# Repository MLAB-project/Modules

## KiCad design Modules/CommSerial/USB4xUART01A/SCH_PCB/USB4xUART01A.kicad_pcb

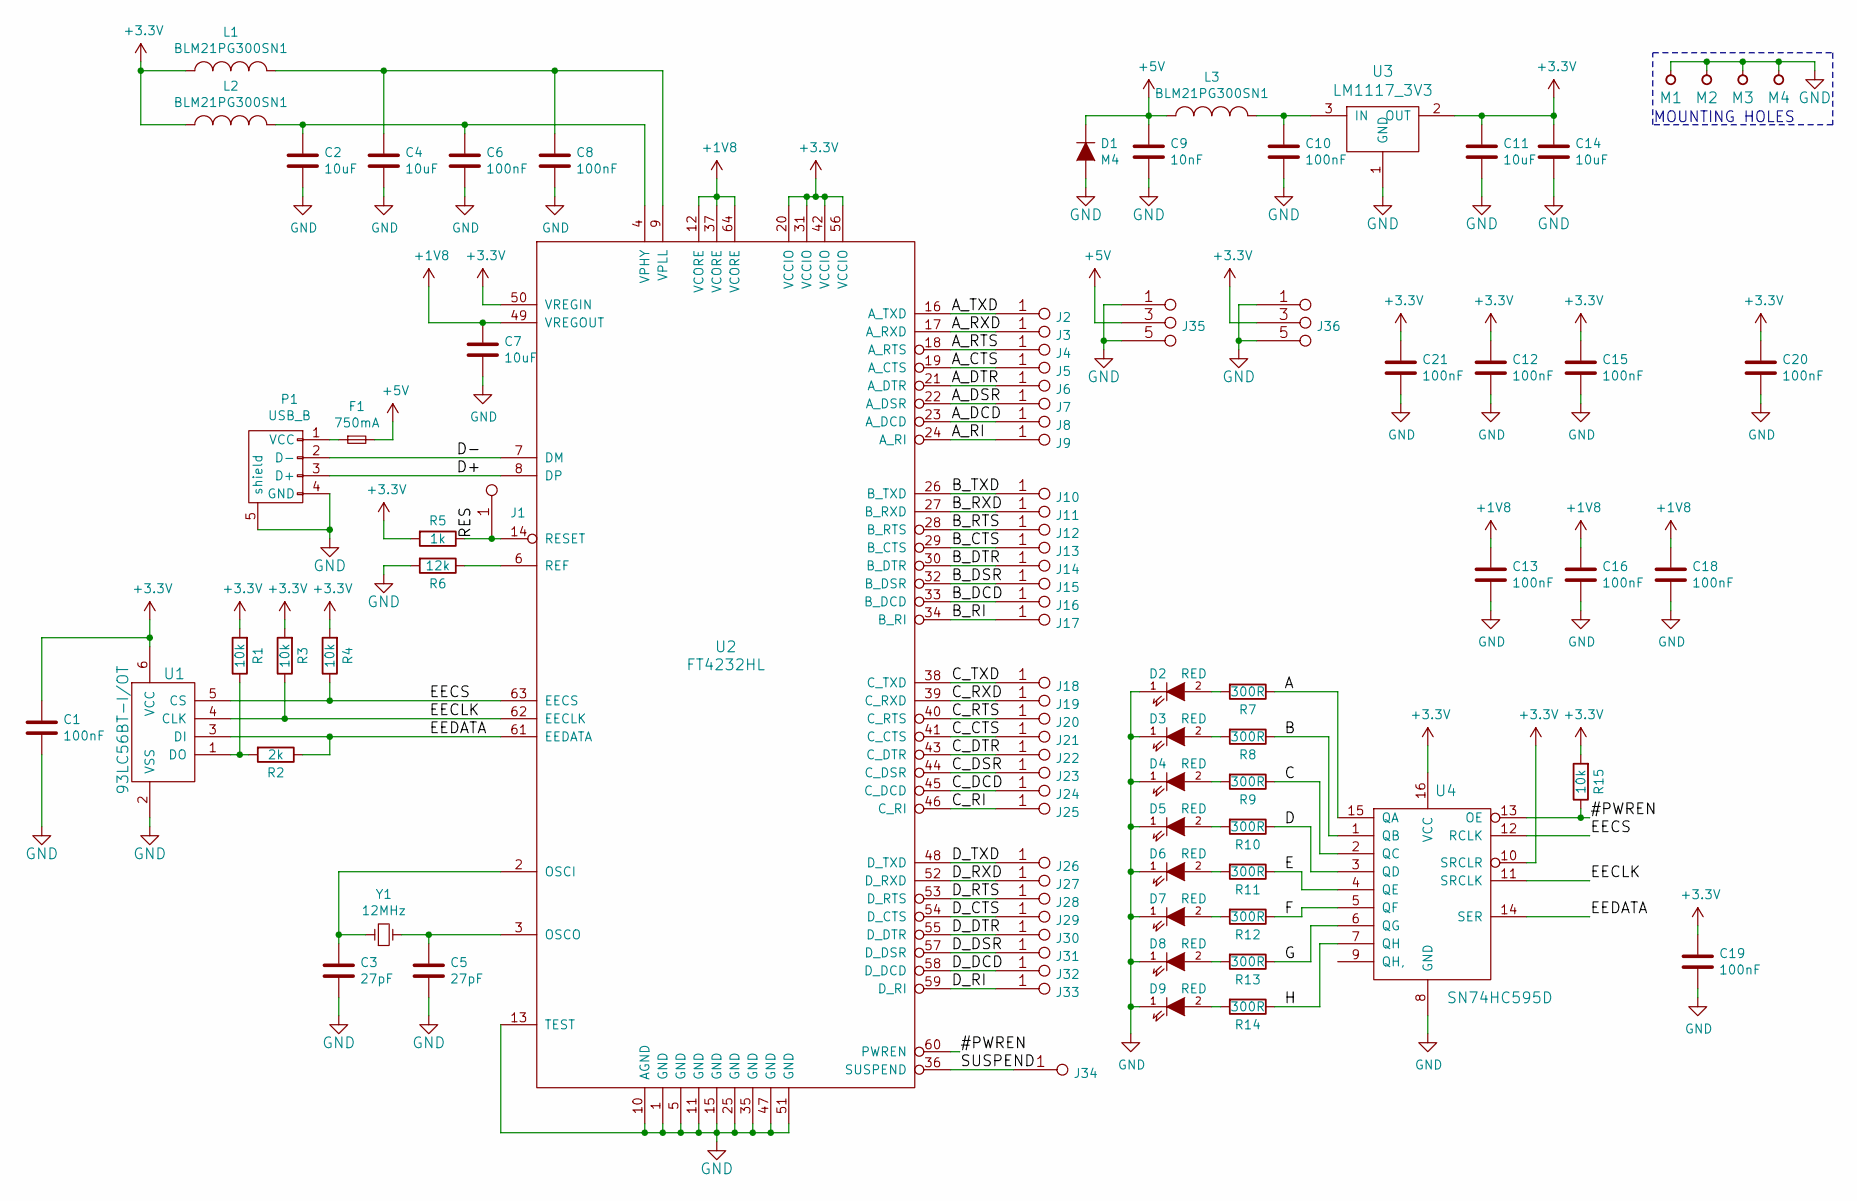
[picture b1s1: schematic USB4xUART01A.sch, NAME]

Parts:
C1, C6, C8, C10, C12, C13, C15, C16, C18, C19, C20, C21: 100nF; SMD-0805
C2, C4, C7, C11, C14: 10uF; SMD-0805
C3, C5: 27pF; SMD-0805
C9: 10nF; SMD-0805
D1: M4; Diode-SMA_Standard
D2, D3, D4, D5, D6, D7, D8, D9: RED; LED_1206
F1: 750mA; 1812
J1, J2, J3, J4, J5, J6, J7, J8, J9, J10, J11, J12, J13, J14, J15, J16, J17, J18, J19, J20, J21, J22, J23, J24, J25, J26, J27, J28, J29, J30, J31, J32, J33, J34: JUMP_2x1; Straight_1x02
J35, J36: JUMP_3X2; Straight_2x03
L1, L2, L3: BLM21PG300SN1; SMD-0805
M1, M2, M3, M4: HOLE; MountingHole_3mm
P1: USB_B
R1, R3, R4, R15: 10k; SMD-0805
R2: 2k; SMD-0805
R5: 1k; SMD-0805
R6: 12k; SMD-0805
R7, R8, R9, R10, R11, R12, R13, R14: 300R; SMD-0805
U1: 93LC56BT-I/OT; SOT-23-6
U2: FT4232HL; LQFP-64_10x10mm_Pitch0.5mm
U3: LM1117_3V3; SOT-223
U4: SN74HC595D; SO-16-N
Y1: 12MHz; Crystal_HC49-U_Vertical

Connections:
+1V8: C7.1, C13.1, C16.1, C18.1, U2.12 (VCORE), U2.37 (VCORE), U2.49 (VREGOUT), U2.64 (VCORE)
+3V3: C1.1, C11.1, C12.1, C14.1, C15.1, C19.1, C20.1, C21.1, J36.3 (4), J36.4, L1.1, L2.1, R1.2, R3.2, R4.2, R5.2, R15.2, U1.6 (VCC), U2.20 (VCCIO), U2.31 (VCCIO), U2.42 (VCCIO), U2.50 (VREGIN), U2.56 (VCCIO), U3.2 (OUT), U3.4 (OUT), U4.10 (SRCLR), U4.16 (VCC)
+5V: C9.1, D1.1 (K), F1.2, J35.3 (4), J35.4, L3.1
/#PWREN: R15.1, U2.60 (PWREN), U4.13 (OE)
/A: R7.1, U4.15 (QA)
/A_CTS: J5.1, J5.2, U2.19 (A_CTS)
/A_DCD: J8.1, J8.2, U2.23 (A_DCD)
/A_DSR: J7.1, J7.2, U2.22 (A_DSR)
/A_DTR: J6.1, J6.2, U2.21 (A_DTR)
/A_RI: J9.1, J9.2, U2.24 (A_RI)
/A_RTS: J4.1, J4.2, U2.18 (A_RTS)
/A_RXD: J3.1, J3.2, U2.17 (A_RXD)
/A_TXD: J2.1, J2.2, U2.16 (A_TXD)
/B: R8.1, U4.1 (QB)
/B_CTS: J13.1, J13.2, U2.29 (B_CTS)
/B_DCD: J16.1, J16.2, U2.33 (B_DCD)
/B_DSR: J15.1, J15.2, U2.32 (B_DSR)
/B_DTR: J14.1, J14.2, U2.30 (B_DTR)
/B_RI: J17.1, J17.2, U2.34 (B_RI)
/B_RTS: J12.1, J12.2, U2.28 (B_RTS)
/B_RXD: J11.1, J11.2, U2.27 (B_RXD)
/B_TXD: J10.1, J10.2, U2.26 (B_TXD)
/C: R9.1, U4.2 (QC)
/C_CTS: J21.1, J21.2, U2.41 (C_CTS)
/C_DCD: J24.1, J24.2, U2.45 (C_DCD)
/C_DSR: J23.1, J23.2, U2.44 (C_DSR)
/C_DTR: J22.1, J22.2, U2.43 (C_DTR)
/C_RI: J25.1, J25.2, U2.46 (C_RI)
/C_RTS: J20.1, J20.2, U2.40 (C_RTS)
/C_RXD: J19.1, J19.2, U2.39 (C_RXD)
/C_TXD: J18.1, J18.2, U2.38 (C_TXD)
/D: R10.1, U4.3 (QD)
/D+: P1.3 (D+), U2.8 (DP)
/D-: P1.2 (D-), U2.7 (DM)
/D_CTS: J29.1, J29.2, U2.54 (D_CTS)
/D_DCD: J32.1, J32.2, U2.58 (D_DCD)
/D_DSR: J31.1, J31.2, U2.57 (D_DSR)
/D_DTR: J30.1, J30.2, U2.55 (D_DTR)
/D_RI: J33.1, J33.2, U2.59 (D_RI)
/D_RTS: J28.1, J28.2, U2.53 (D_RTS)
/D_RXD: J27.1, J27.2, U2.52 (D_RXD)
/D_TXD: J26.1, J26.2, U2.48 (D_TXD)
/E: R11.1, U4.4 (QE)
/EECLK: R3.1, U1.4 (CLK), U2.62 (EECLK), U4.11 (SRCLK)
/EECS: R4.1, U1.5 (CS), U2.63 (EECS), U4.12 (RCLK)
/EEDATA: R2.1, U1.3 (DI), U2.61 (EEDATA), U4.14 (SER)
/F: R12.1, U4.5 (QF)
/G: R13.1, U4.6 (QG)
/H: R14.1, U4.7 (QH)
/RES: J1.1, J1.2, R5.1, U2.14 (RESET)
/SUSPEND: J34.1, J34.2, U2.36 (SUSPEND)
GND: C1.2, C2.2, C3.2, C4.2, C5.2, C6.2, C7.2, C8.2, C9.2, C10.2, C11.2, C12.2, C13.2, C14.2, C15.2, C16.2, C18.2, C19.2, C20.2, C21.2, D1.2 (A), D2.1 (K), D3.1 (K), D4.1 (K), D5.1 (K), D6.1 (K), D7.1 (K), D8.1 (K), D9.1 (K), J35.1 (2), J35.2, J35.5 (6), J35.6, J36.1 (2), J36.2, J36.5 (6), J36.6, M1.1, M2.1, M3.1, M4.1, P1.4 (GND), P1.5 (shield), R6.2, U1.2 (VSS), U2.1 (GND), U2.5 (GND), U2.10 (AGND), U2.11 (GND), U2.13 (TEST), U2.15 (GND), U2.25 (GND), U2.35 (GND), U2.47 (GND), U2.51 (GND), U3.1 (GND), U4.8 (GND)
unnamed: C2.1, C6.1, L2.2, U2.4 (VPHY)
unnamed: C3.1, U2.2 (OSCI), Y1.1
unnamed: C4.1, C8.1, L1.2, U2.9 (VPLL)
unnamed: C5.1, U2.3 (OSCO), Y1.2
unnamed: C10.1, L3.2, U3.3 (IN)
unnamed: D2.2 (A), R7.2
unnamed: D3.2 (A), R8.2
unnamed: D4.2 (A), R9.2
unnamed: D5.2 (A), R10.2
unnamed: D6.2 (A), R11.2
unnamed: D7.2 (A), R12.2
unnamed: D8.2 (A), R13.2
unnamed: D9.2 (A), R14.2
unnamed: F1.1, P1.1 (VCC)
unnamed: R1.1, R2.2, U1.1 (DO)
unnamed: R6.1, U2.6 (REF)

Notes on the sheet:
MOUNTING HOLES

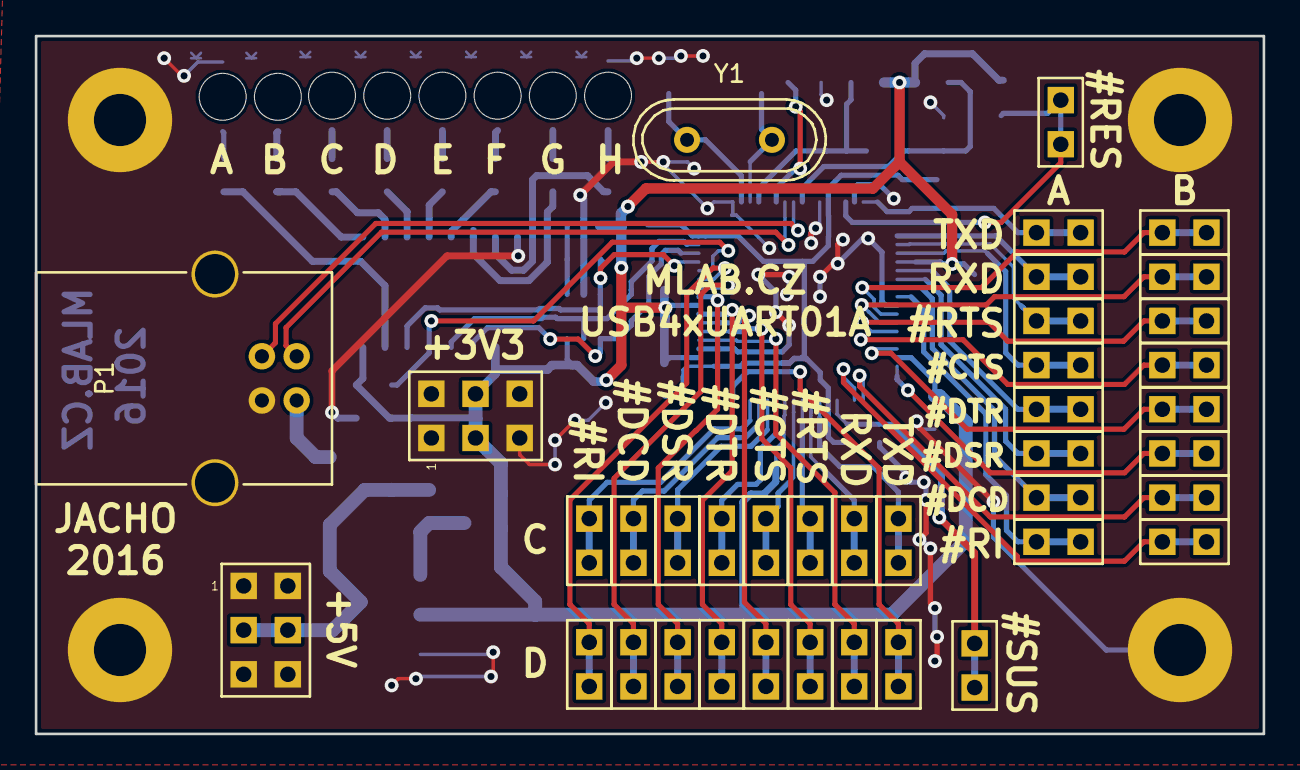
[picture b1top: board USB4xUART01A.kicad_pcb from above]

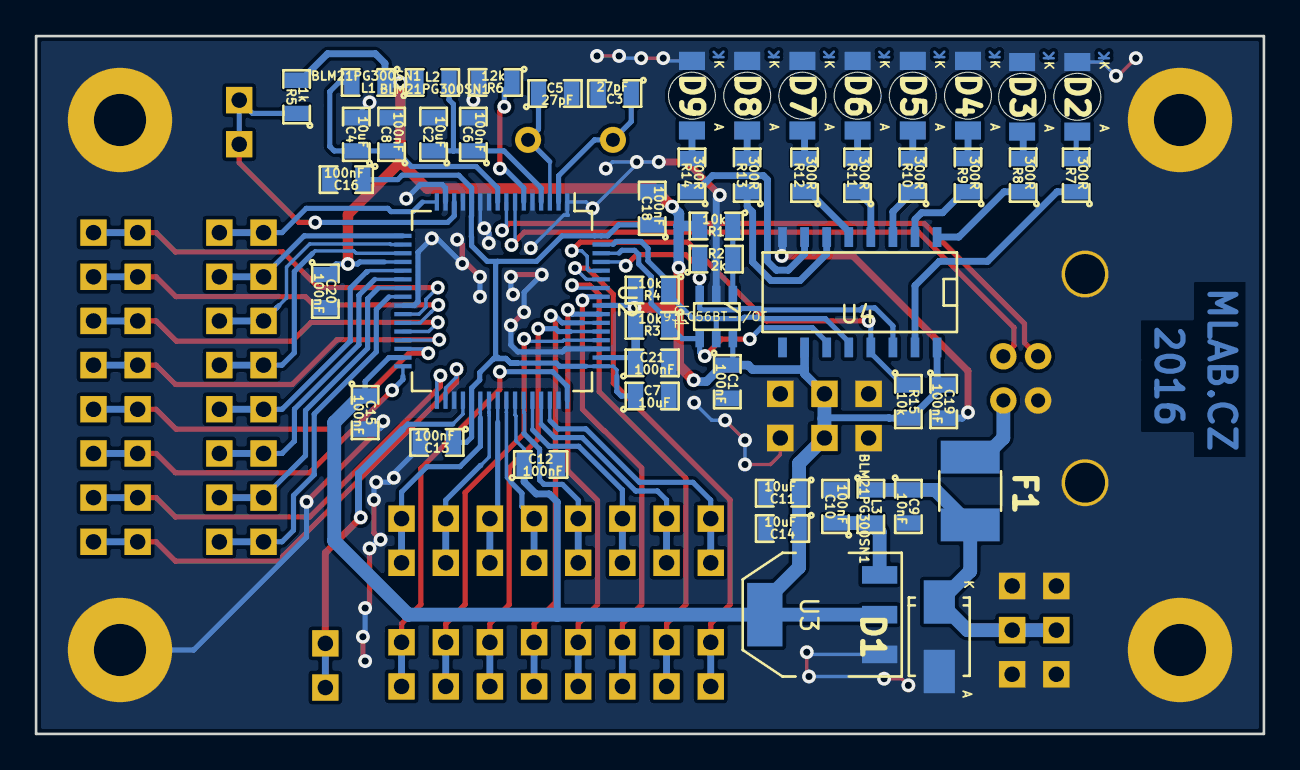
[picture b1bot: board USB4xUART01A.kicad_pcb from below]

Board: 2 copper layers, 70.6 x 40.1 mm, 94 parts (52 on the bottom side), 68 nets.

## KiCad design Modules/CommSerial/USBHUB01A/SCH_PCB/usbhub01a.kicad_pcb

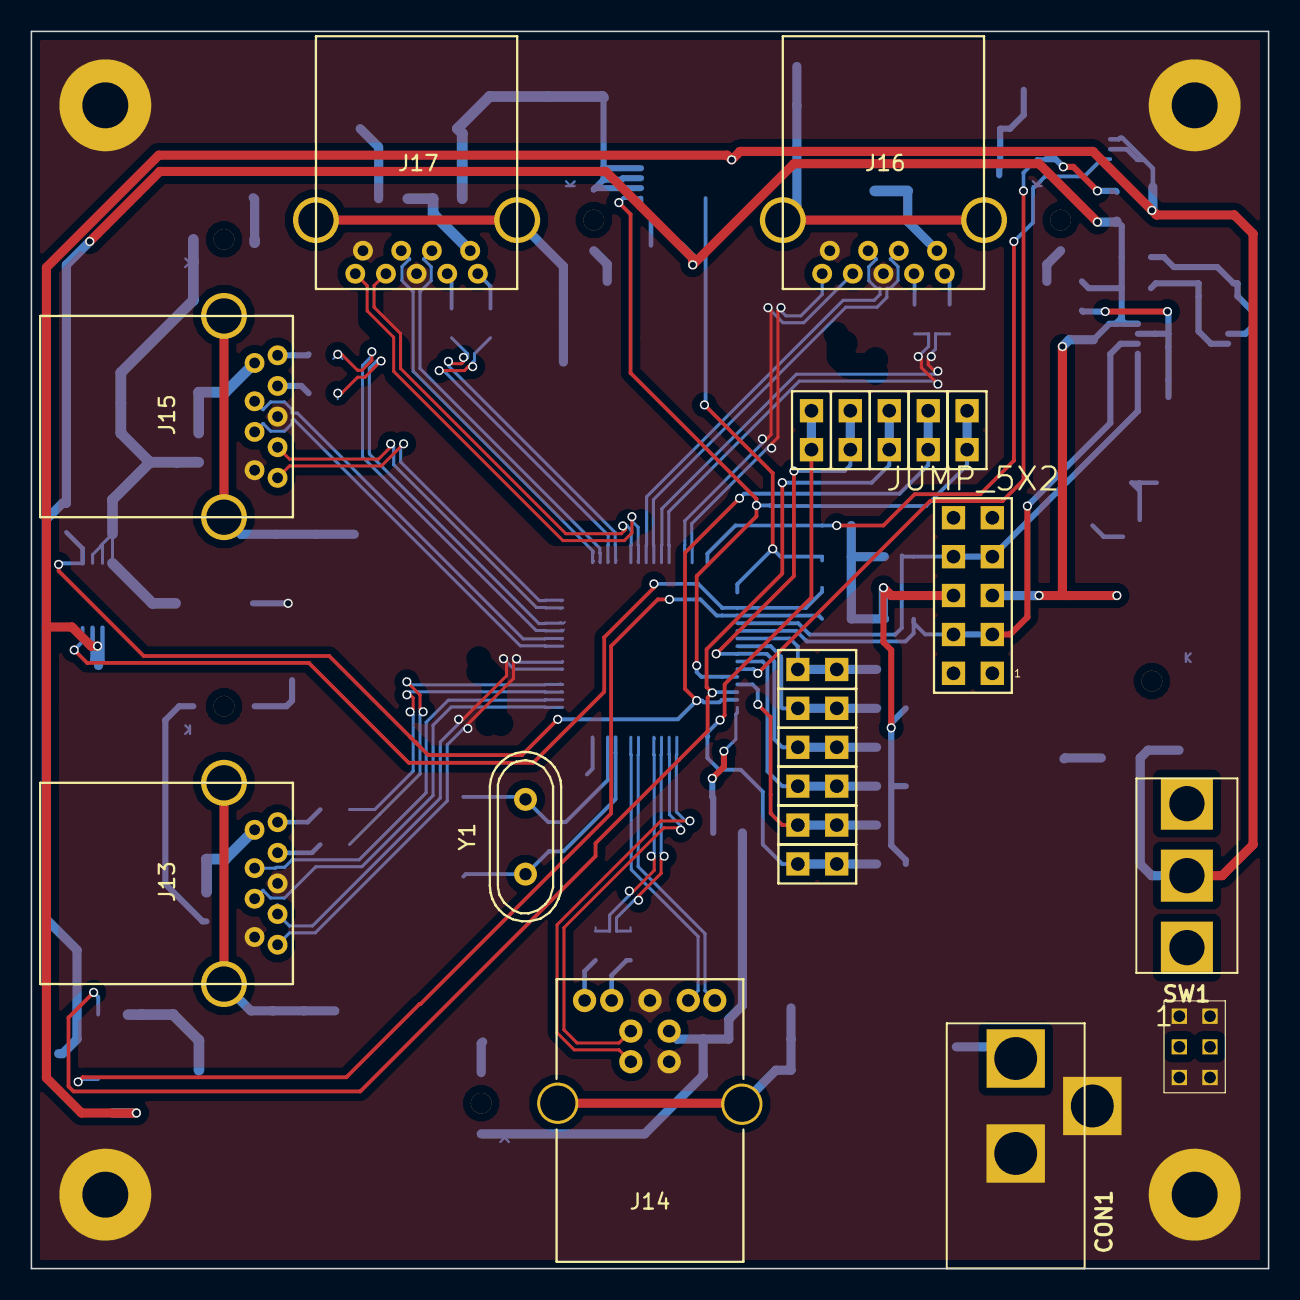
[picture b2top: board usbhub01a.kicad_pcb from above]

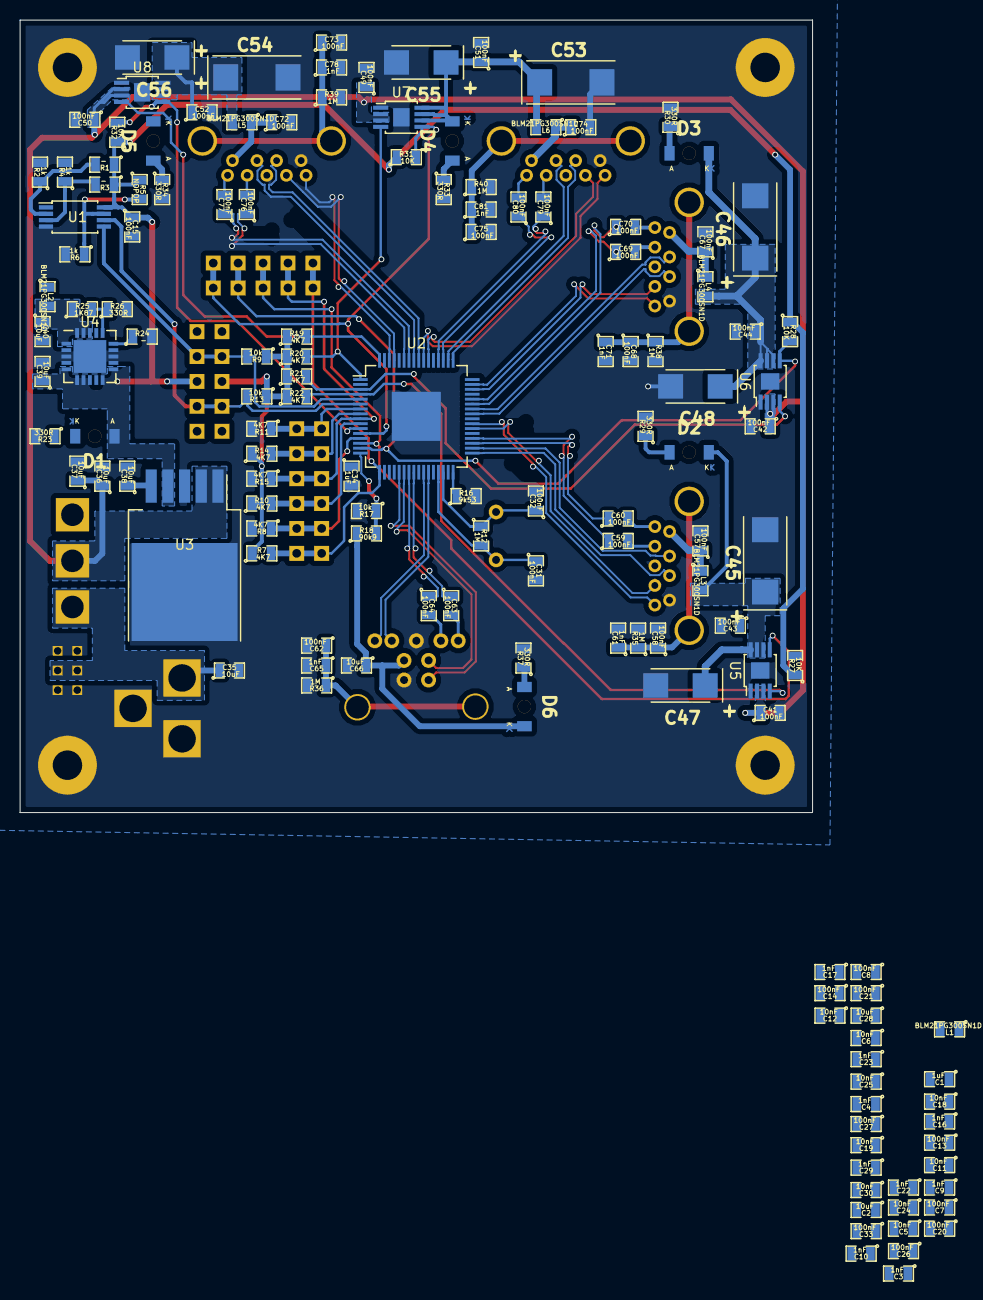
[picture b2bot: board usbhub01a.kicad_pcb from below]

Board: 4 copper layers, 80.8 x 80.8 mm, 166 parts (141 on the bottom side), 96 nets.

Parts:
C1, C34: 1uF; SMD-0805
C2, C28, C35, C36, C37, C38, C39, C40, C66: 10uF; SMD-0805
C3, C4, C9, C10, C16, C17, C22, C23, C29, C61, C65, C71, C78, C81: 1nF; SMD-0805
C5, C6, C11, C12, C18, C19, C24, C25, C30: 10nF; SMD-0805
C7, C8, C13, C14, C15, C20, C21, C26, C27, C31, C32, C33, C41, C42, C43, C44, C49, C50, C51, C52, C57, C58, C59, C60, C62, C63, C64, C67, C68, C69, C70, C72, C73, C74, C75, C76, C77, C79, C80: 100nF; SMD-0805
C45, C46, C53, C54: 100uF; TantalC_SizeD_Reflow
C47, C48, C55, C56: 47uF; TantalC_SizeC_Reflow
CON1: BARREL_JACK; DC2,1MM
D1, D2, D3, D4, D5: LED; LED_1206
D6: GREEN; LED_1206
J1, J2, J3, J4, J5, J6, J7, J8, J9, J10, J11: JUMP_2x1; Straight_2x01
J12: JUMP_5X2; Straight_2x05
J13, J15, J16, J17: USB3_A; USB3_0_A
J14: USB3_B; USB3_0_B
J18: JUMP_3X2; Straight_2x03
L1, L2, L3, L4, L5, L6: BLM21PG300SN1D; SMD-0805
M1, M2, M3, M4: HOLE; MountingHole_3mm
R1, R3, R24: -; SMD-0805
R2, R4, R6: 1k; SMD-0805
R5: NOPOP; SMD-0805
R7, R8, R10, R11, R14, R15, R19, R20, R21, R22: 4K7; SMD-0805
R9, R13, R17: 10k; SMD-0805
R12, R35, R36, R38, R39, R40: 1M; SMD-0805
R16: 9k53; SMD-0805
R18: 90k9; SMD-0805
R23, R26, R29, R30, R33, R34, R37: 330R; SMD-0805
R25: 1K87; SMD-0805
R27, R28, R31, R32: 10K; SMD-0805
SW1: SPST; Prepinaci_3A_SL19121
U1: CAT24C04YI-GT3OSCT-ND; TSSOP-8_4.4x3mm_Pitch0.65mm
U2: TUSB8041IPAPRQ1; HTQFP-64_10x10mm_Pitch0.5mm
U3: TPS7A4533KTTR; TO-263-5
U4: TPS74801RGWR; QFN-20-1EP_5x5mm_Pitch0.65mm
U5, U6, U7, U8: TPS2001CDGN; MSOP-8-1EP_3x3mm_Pitch0.65mm
Y1: 24MHz; Crystal_HC49-U_Vertical

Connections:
+1V1: C40.1, L2.2, R25.1, U4.1, U4.18, U4.19, U4.20
+3V3: C15.1, C39.1, D1.1, J12.5, J12.6, L1.2, R1.1, R3.1, R5.1, R7.1, R9.1, R10.1, R13.1, R14.1, R19.1, R20.1, R21.1, R22.1, R27.1, R28.1, R31.1, R32.1, U1.8, U3.4, U4.5, U4.6, U4.7, U4.8, U4.10, U4.11
+5V: C36.1, C37.1, C41.1, C42.1, C49.1, C50.1, SW1.2, U3.1, U3.2, U5.2, U5.3, U6.2, U6.3, U7.2, U7.3, U8.2, U8.3
/AUTOENZ_HS_SUS: J11.1, J11.2, R8.1, U2.13
/DOWNSTREAM PORT POWER SWITCHES/DN1_VBUS: C45.1, C47.1, D2.2, L3.2, U5.6, U5.7, U5.8
/DOWNSTREAM PORT POWER SWITCHES/DN2_VBUS: C44.1, C46.1, C48.1, D3.2, L4.2, U6.6, U6.7, U6.8
/DOWNSTREAM PORT POWER SWITCHES/DN3_VBUS: C51.1, C53.1, C55.1, D4.2, L6.2, U7.6, U7.7, U7.8
/DOWNSTREAM PORT POWER SWITCHES/DN4_VBUS: C52.1, C54.1, C56.1, D5.2, L5.2, U8.6, U8.7, U8.8
/DOWNSTREAM PORT POWER SWITCHES/OVERCUR1Z_TDI: J3.1, J3.2, R27.2, U2.14, U5.5
/DOWNSTREAM PORT POWER SWITCHES/OVERCUR2Z_TMS: J4.1, J4.2, R28.2, U2.15, U6.5
/DOWNSTREAM PORT POWER SWITCHES/OVERCUR3Z_TCK: J5.1, J5.2, R31.2, U2.12, U7.5
/DOWNSTREAM PORT POWER SWITCHES/OVERCUR4Z: R32.2, U2.11, U8.5
/DOWNSTREAM PORT POWER SWITCHES/PWRON1_BATEN1: R22.2, U2.4, U5.4
/DOWNSTREAM PORT POWER SWITCHES/PWRON2_BATEN2: R21.2, U2.3, U6.4
/DOWNSTREAM PORT POWER SWITCHES/PWRON3_BATEN3: R20.2, U2.1, U7.4
/DOWNSTREAM PORT POWER SWITCHES/PWRON4_BATEN4: R19.2, U2.64, U8.4
/FULLPWRMGMTZ_SMBA1: J8.1, J8.2, R14.2, U2.8
/GANGED_SMBA2_SH_UP: J7.1, J7.2, R10.2, U2.10
/IO1V1: C2.1, C4.1, C6.1, C8.1, C10.1, C12.1, C14.1, C17.1, C19.1, C21.1, C23.1, C25.1, C27.1, C28.1, C29.1, C30.1, C33.1, L2.1, U2.19, U2.25, U2.37, U2.45, U2.53, U2.60, U2.63
/IO3V3: C1.1, C3.1, C5.1, C7.1, C9.1, C11.1, C13.1, C16.1, C18.1, C20.1, C22.1, C24.1, C26.1, L1.1, U2.2, U2.20, U2.31, U2.48
/PWRCTL_POL_TDO: J2.1, J2.2, J9.1, J9.2, R15.1, U2.9
/SCL: J12.3, J12.4, R13.2, U1.6, U2.6
/SDA: J12.7, J12.8, R9.2, U1.5, U2.5
/SMBUSZ_SS_SUS: J10.1, J10.2, R11.1, U2.7
/TEST_TRSTZ: J1.1, J1.2, J6.1, J6.2, R7.2, U2.17
/USBPORT/USB_DM_DN1+: J13.2, U2.34
/USBPORT/USB_DM_DN1-: J13.3, U2.33
/USBPORT/USB_DM_DN2+: J15.2, U2.42
/USBPORT/USB_DM_DN2-: J15.3, U2.41
/USBPORT/USB_DM_DN3+: J17.2, U2.50
/USBPORT/USB_DM_DN3-: J17.3, U2.49
/USBPORT/USB_DM_DN4+: J16.2, U2.57
/USBPORT/USB_DM_DN4-: J16.3, U2.56
/USBPORT/USB_DM_UP+: J14.2, U2.22
/USBPORT/USB_DM_UP-: J14.3, U2.21
/USBPORT/USB_SSRXM_DN1+: J13.5, U2.39
/USBPORT/USB_SSRXM_DN1-: J13.6, U2.38
/USBPORT/USB_SSRXM_DN2+: J15.5, U2.47
/USBPORT/USB_SSRXM_DN2-: J15.6, U2.46
/USBPORT/USB_SSRXM_DN3+: J17.5, U2.55
/USBPORT/USB_SSRXM_DN3-: J17.6, U2.54
/USBPORT/USB_SSRXM_DN4+: J16.5, U2.62
/USBPORT/USB_SSRXM_DN4-: J16.6, U2.61
/USBPORT/USB_SSRXM_UP+: J14.8, U2.27
/USBPORT/USB_SSRXM_UP-: J14.9, U2.26
/USBPORT/USB_SSTXM_DN1+: C59.1, U2.36
/USBPORT/USB_SSTXM_DN1-: C60.1, U2.35
/USBPORT/USB_SSTXM_DN2+: C69.1, U2.44
/USBPORT/USB_SSTXM_DN2-: C70.1, U2.43
/USBPORT/USB_SSTXM_DN3+: C79.1, U2.52
/USBPORT/USB_SSTXM_DN3-: C80.1, U2.51
/USBPORT/USB_SSTXM_DN4+: C76.1, U2.59
/USBPORT/USB_SSTXM_DN4-: C77.1, U2.58
/USBPORT/USB_SSTXM_UP+: C63.1, U2.24
/USBPORT/USB_SSTXM_UP-: C64.1, U2.23
/USBPORT/USB_VBUS_UP: C66.1, D6.2, J14.1, R18.1
GND: C1.2, C3.2, C5.2, C7.2, C9.2, C11.2, C13.2, C15.2, C16.2, C18.2, C20.2, C22.2, C24.2, C26.2, C31.2, C32.2, C34.2, C35.2, C36.2, C37.2, C38.2, C39.2, C40.2, C41.2, C42.2, C43.2, C44.2, C45.2, C46.2, C47.2, C48.2, C49.2, C50.2, C51.2, C52.2, C53.2, C54.2, C55.2, C56.2, C57.2, C58.2, C61.2, C62.2, C65.2, C66.2, C67.2, C68.2, C71.2, C72.2, C73.2, C74.2, C75.2, C78.2, C81.2, CON1.2, CON1.3, J13.4, J13.7, J14.4, J14.7, J15.4, J15.7, J16.4, J16.7, J17.4, J17.7, J18.1, J18.2, J18.5, J18.6, M1.1, M2.1, M3.1, M4.1, R2.2, R4.2, R6.2, R8.2, R11.2, R15.2, R16.2, R17.2, R23.2, R24.2, R26.2, R29.2, R30.2, R33.2, R34.2, R35.2, R36.2, R37.2, R38.2, R39.2, R40.2, U1.4, U2.65, U3.3, U4.2, U4.3, U4.4, U4.12, U4.13, U4.14, U4.21, U5.1, U5.9, U6.1, U6.9, U7.1, U7.9, U8.1, U8.9
unnamed: C2.2, C4.2, C6.2, C8.2, C10.2, C12.2, C14.2, C17.2, C19.2, C21.2, C23.2, C25.2, C27.2, C28.2, C29.2, C30.2, C33.2
unnamed: C31.1, R12.2, U2.29, Y1.1
unnamed: C32.1, R12.1, U2.30, Y1.2
unnamed: C34.1, U2.18
unnamed: C35.1, CON1.1, J18.3, J18.4, SW1.1
unnamed: C38.1, U3.5
unnamed: C57.1, J13.1, L3.1
unnamed: C58.1, C61.1, J13.10, R35.1
unnamed: C59.2, J13.8
unnamed: C60.2, J13.9
unnamed: C62.1, C65.1, J14.10, R36.1
unnamed: C63.2, J14.5
unnamed: C64.2, J14.6
unnamed: C67.1, J15.1, L4.1
unnamed: C68.1, C71.1, J15.10, R38.1
unnamed: C69.2, J15.8
unnamed: C70.2, J15.9
unnamed: C72.1, J16.1, L5.1
unnamed: C73.1, C78.1, J16.10, R39.1
unnamed: C74.1, J17.1, L6.1
unnamed: C75.1, C81.1, J17.10, R40.1
unnamed: C76.2, J16.8
unnamed: C77.2, J16.9
unnamed: C79.2, J17.8
unnamed: C80.2, J17.9
unnamed: D1.2, R23.1
unnamed: D2.1, R29.1
unnamed: D3.1, R30.1
unnamed: D4.1, R33.1
unnamed: D5.1, R34.1
unnamed: D6.1, R37.1
unnamed: J12.1, J12.2, J12.9, J12.10
unnamed: R1.2, R2.1, U1.2
unnamed: R3.2, R4.1, U1.3
unnamed: R5.2, R6.1, U1.7
unnamed: R16.1, U2.32
unnamed: R17.1, R18.2, U2.16
unnamed: R24.1, U4.15
unnamed: R25.2, R26.1, U4.16

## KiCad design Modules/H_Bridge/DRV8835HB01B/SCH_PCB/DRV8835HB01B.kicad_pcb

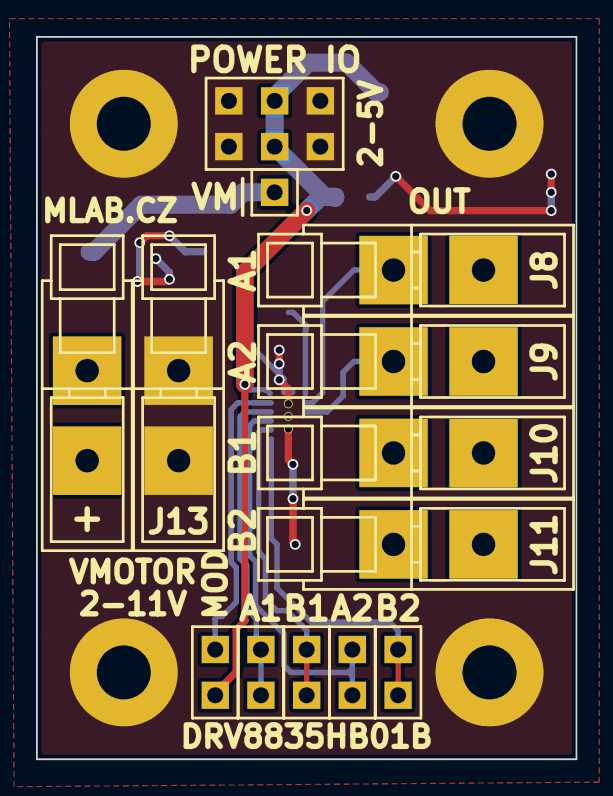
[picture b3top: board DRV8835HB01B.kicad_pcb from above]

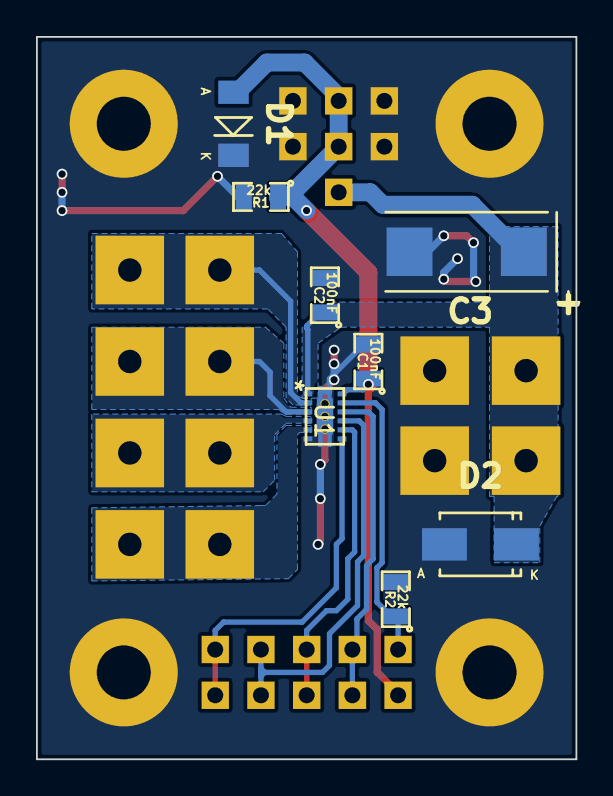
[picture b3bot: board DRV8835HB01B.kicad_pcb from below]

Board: 2 copper layers, 30.0 x 40.1 mm, 25 parts (8 on the bottom side), 12 nets.

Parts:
C1, C2: 100nF; SMD-0805
C3: 100uF; TantalC_SizeD_Reflow
D1: BZV55C-5,6V; Diode-MiniMELF_Standard
D2: M4; Diode-SMA_Standard
J1: JUMP_3X2; Straight_2x03
J2: CONN1_1; Straight_1x01
J3, J4, J5, J6: JUMP_2x1; Straight_2x01
J7: JUMP2_2x1; Straight_2x01
J8, J9, J10, J11, J12, J13: WAGO256
M1, M2, M3, M4: HOLE; MountingHole_3mm
R1, R2: 22k; SMD-0805
U1: DRV8835; WSON-12

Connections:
/AIN1: J3.1, J3.2, U1.10
/AIN2: J4.1, J4.2, U1.9
/AOUT1: J8.1, U1.2
/AOUT2: J9.1, U1.3
/BIN1: J5.1, J5.2, U1.8
/BIN2: J6.1, J6.2, U1.7
/BOUT1: J10.1, U1.4
/BOUT2: J11.1, U1.5
/VM: C2.1, C3.1, D2.2, J2.1, J12.1, U1.1
GND: C1.2, C2.2, C3.2, D1.2, D2.1, J1.1, J1.2, J1.5, J1.6, J13.1, M1.1, M2.1, M3.1, M4.1, R1.2, R2.2, U1.6
unnamed: J7.1, R2.1, U1.11
VCC: C1.1, D1.1, J1.3, J1.4, J7.2, R1.1, U1.12

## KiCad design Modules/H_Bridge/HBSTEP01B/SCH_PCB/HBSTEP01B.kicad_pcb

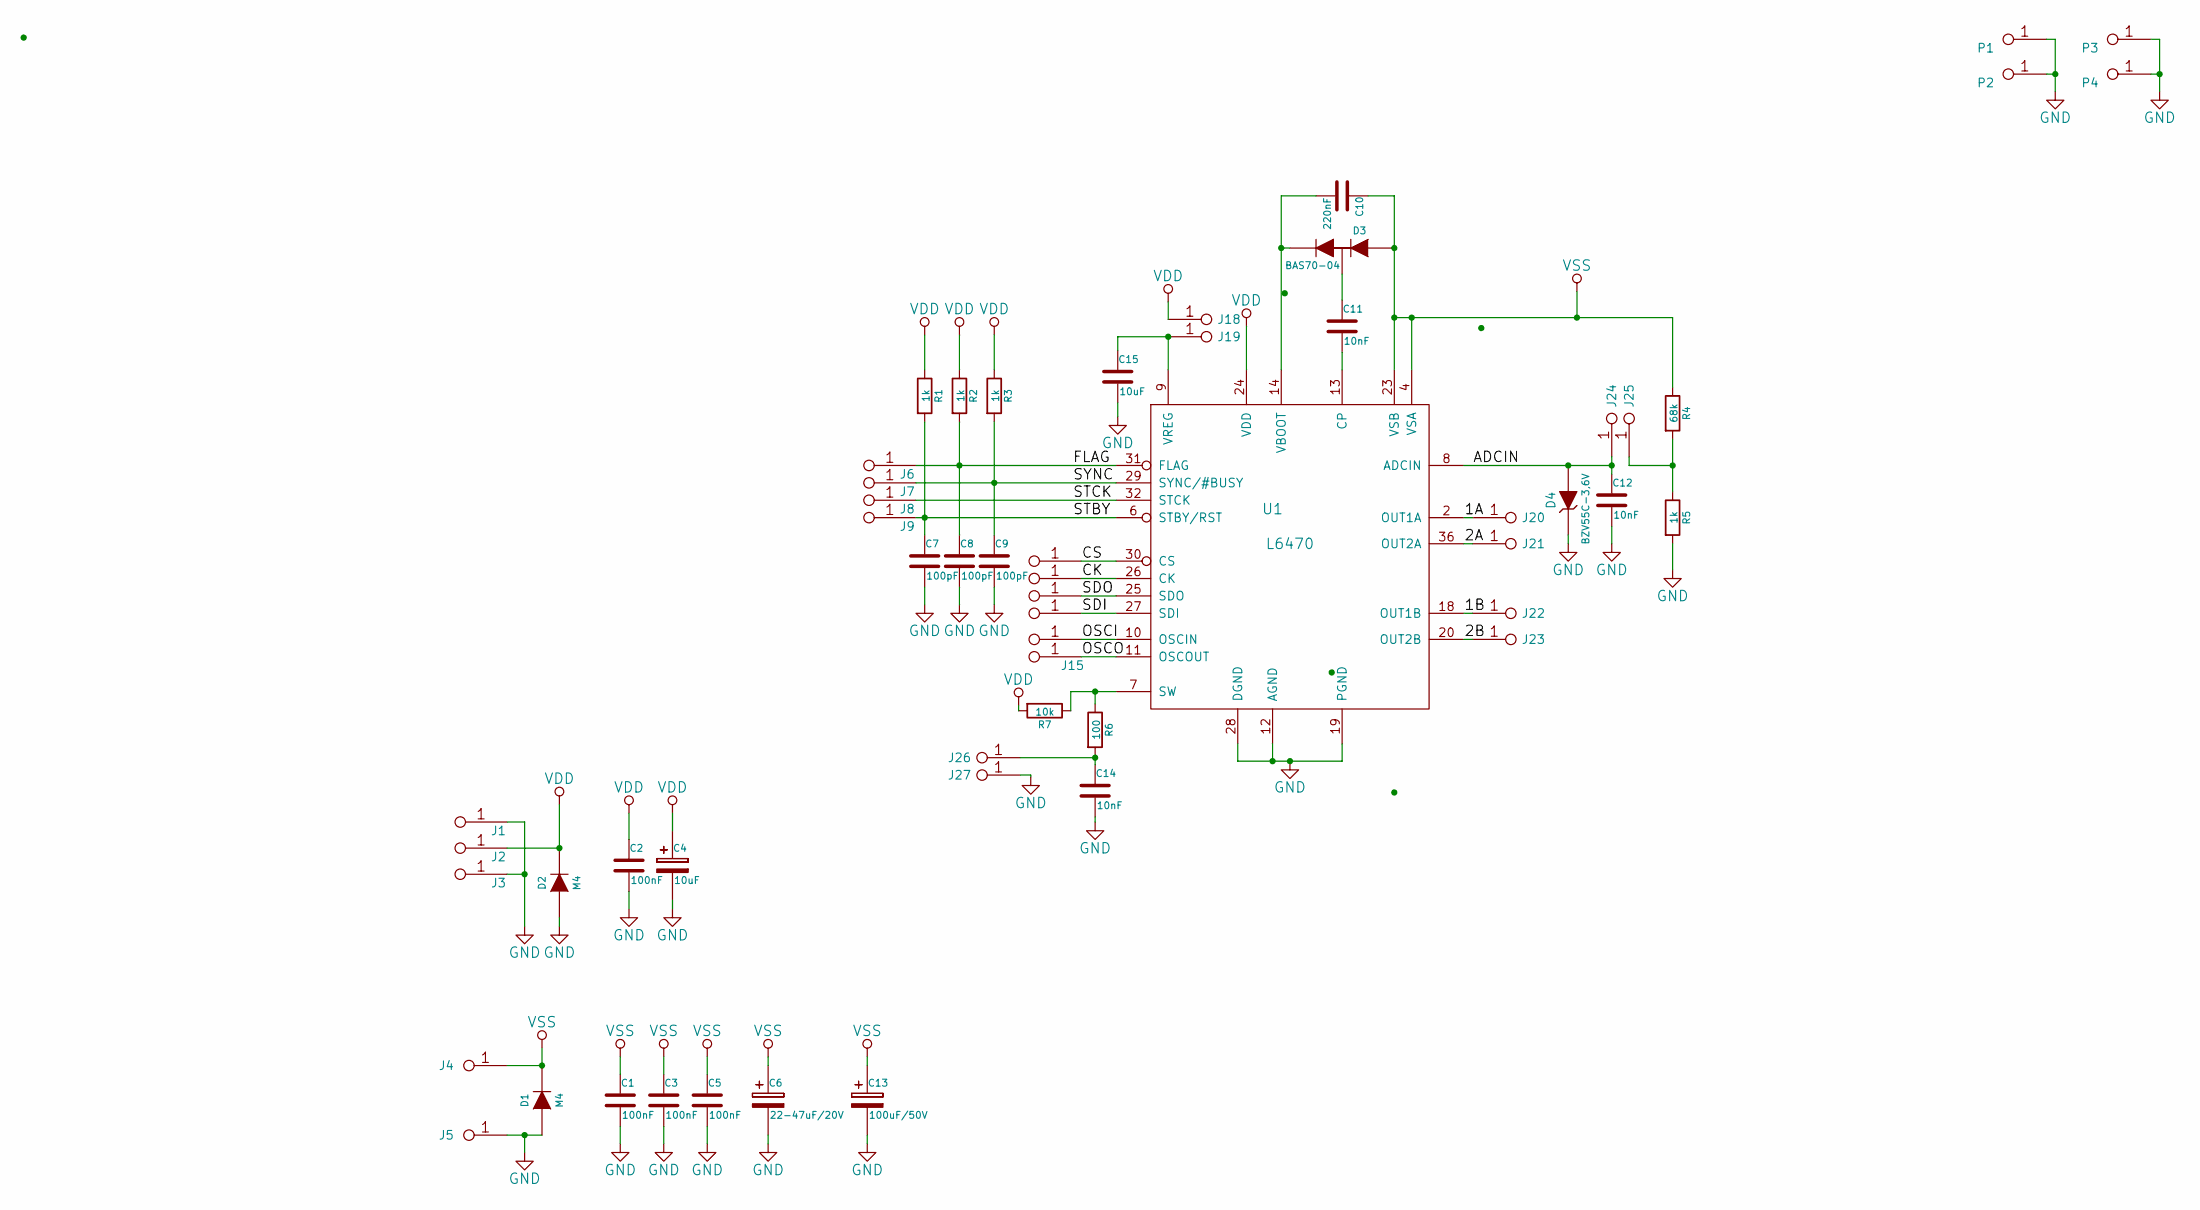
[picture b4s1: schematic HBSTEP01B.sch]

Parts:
C1, C2, C3, C5: 100nF; SMD-0805
C4: 10uF; TantalC_SizeB_Reflow
C6: 22-47uF/20V; TantalC_SizeC_Reflow
C7, C8, C9: 100pF; SMD-0805
C10: 220nF; SMD-0805
C11, C12, C14: 10nF; SMD-0805
C13: 100uF/50V; Elko_vert_11x5mm_RM2_CopperClear
C15: 10uF; SMD-0805
D1, D2: M4; SMA_Standard
D3: BAS70-04; SOT-23
D4: BZV55C-3,6V; MiniMELF_Standard
J1, J2, J3, J6, J7, J8, J9, J10, J11, J12, J13, J14, J15: JUMP_2x1; Straight_2x01
J4, J5: CONN1_1; WAGO256
J18, J19, J24, J25, J26, J27: CONN1_1; Straight_1x01
J20, J21, J22, J23: CONN1_1; WAGO256_2
P1, P2, P3, P4: sroub; MountingHole_3mm
R1, R2, R3, R5: 1k; SMD-0805
R4: 68k; SMD-0805
R6: 100; SMD-0805
R7: 10k; SMD-0805
U1: L6470; POWERSO36

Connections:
/1A: J20.1, U1.2 (OUT1A), U1.3 (OUT1A)
/1B: J22.1, U1.17 (OUT1B), U1.18 (OUT1B)
/2A: J21.1, U1.35 (OUT2A), U1.36 (OUT2A)
/2B: J23.1, U1.20 (OUT2B), U1.21 (OUT2B)
/ADCIN: C12.1, D4.2 (A), J24.1, U1.8 (ADCIN)
/CK: J11.1, J11.2, U1.26 (CK)
/CS: J10.1, J10.2, U1.30 (CS)
/FLAG: C8.1, J6.1, J6.2, R2.2, U1.31 (FLAG)
/OSCI: J14.1, J14.2, U1.10 (OSCIN)
/OSCO: J15.1, J15.2, U1.11 (OSCOUT)
/SDI: J13.1, J13.2, U1.27 (SDI)
/SDO: J12.1, J12.2, U1.25 (SDO)
/STBY: C7.1, J9.1, J9.2, R1.2, U1.6 (STBY/RST)
/STCK: J8.1, J8.2, U1.32 (STCK)
/SYNC: C9.1, J7.1, J7.2, R3.2, U1.29 (SYNC/#BUSY)
GND: C1.2, C2.2, C3.2, C4.2, C5.2, C6.2, C7.2, C8.2, C9.2, C12.2, C13.2, C14.2, C15.2, D1.1 (A), D2.1 (A), D4.1 (K), J1.1, J1.2, J3.1, J3.2, J5.1, J27.1, P1.1, P2.1, P3.1, P4.1, R5.2, U1.1 (PGND), U1.12 (AGND), U1.19 (PGND), U1.28 (DGND), U1.50 (PGND), U1.51 (PGND), U1.52 (PGND)
unnamed: C10.2, D3.2 (A), U1.14 (VBOOT)
unnamed: C11.1, D3.3 (m)
unnamed: C11.2, U1.13 (CP)
unnamed: C14.1, J26.1, R6.2
unnamed: C15.1, J19.1, U1.9 (VREG)
unnamed: J25.1, R4.2, R5.1
unnamed: R6.1, R7.1, U1.7 (SW)
VDD: C2.1, C4.1, D2.2 (K), J2.1, J2.2, J18.1, R1.1, R2.1, R3.1, R7.2, U1.24 (VDD)
VSS: C1.1, C3.1, C5.1, C6.1, C10.1, C13.1, D1.2 (K), D3.1 (A), J4.1, R4.1, U1.4 (VSA), U1.5 (VSA), U1.15 (VSB), U1.16 (VSB), U1.22 (VSB), U1.23 (VSB), U1.33 (VSA), U1.34 (VSA)

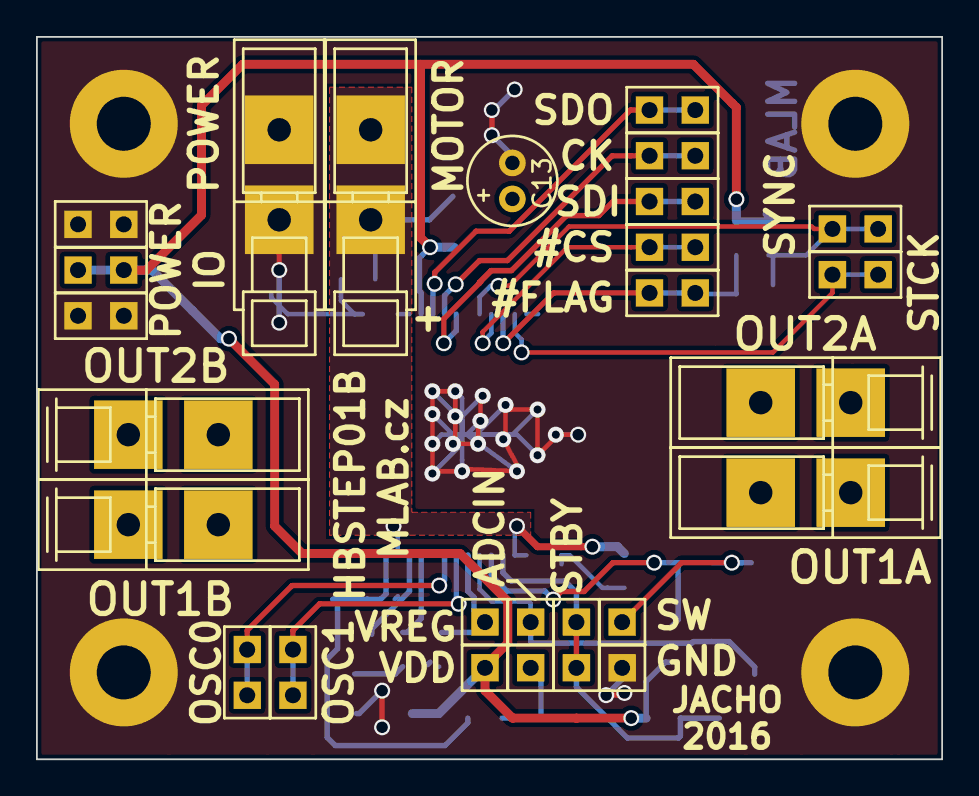
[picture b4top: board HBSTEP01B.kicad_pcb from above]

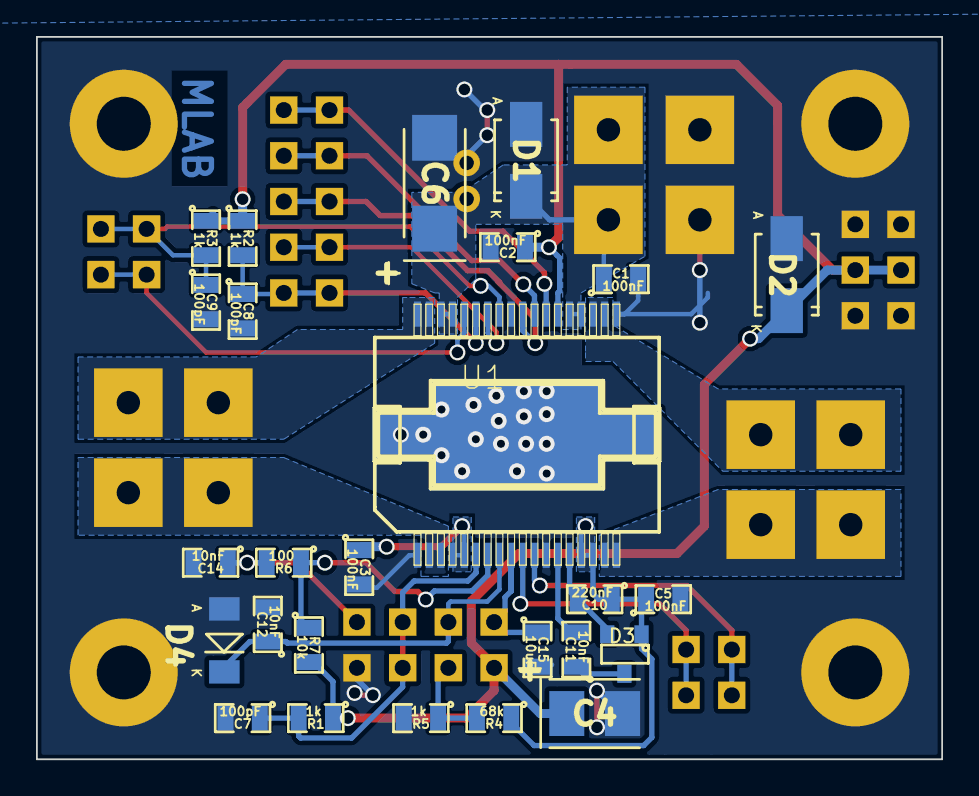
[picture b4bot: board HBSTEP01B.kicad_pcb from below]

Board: 2 copper layers, 50.3 x 40.1 mm, 56 parts (26 on the bottom side), 25 nets.
